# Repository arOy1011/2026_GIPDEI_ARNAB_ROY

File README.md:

<p align="center">📟 NAPPNU Motion Data Recorder</p>

<p align="center">
Bluetooth-enabled Motion Data Logger built using the <b>Seeed XIAO nRF52840 Sense</b>.
</p>
---

# 🛠 Hardware Components

| Component | Quantity |
|-----------|:--------:|
| Seeed XIAO nRF52840 Sense | 1 |
| DS3231 RTC Module | 1 |
| microSD Card Module | 1 |
| microSD Card (FAT32) | 1 |
| Push Button | 1 |
| Li-Po Battery (3.7 V) | 1 |
| USB Type-C Cable | 1 |

---
<div style="page-break-after: always;"></div>

# 📂 Project Structure

```text
main-folder/
│
├── Mobile Application/
│.  └── motion-logger
│      		└── files.....
│
├── Code-Hardware/
│   └── Data_Logger.ino
│
├── PCB Design/
│   └── KiCAD.zip
│
├── Python-Script/
│   └── connect.py
│
└── README files
```

---

# 💻 Software Requirements

## Firmware Development

- Arduino IDE 2.x
- Seeed nRF52 Board Package

### Required Arduino Libraries

- Adafruit Bluefruit nRF52 Libraries
- LSM6DS3
- SdFat
- RTClib
- Wire
- SPI
- EEPROM

---
<div style="page-break-after: always;"></div>

## 📦 Project Files

All required project files are available in the shared Google Drive folder below.

> 📁 **Download Project Files**  
> https://drive.google.com/drive/folders/1yOiiscPsLclZifj_FWon-T-I5wJ6or7X?usp=drive_link

The folder contains:

- 📱 Pre-built Android APK
- 📱 Flutter source code

---

## 📱 Option 1 — Install the Pre-built APK (Recommended)

1. Open the **Google Drive** folder above.
2. Navigate to:

```
Android-Application/
└── motion_logger/
    └── build/
        └── app/
            └── outputs/
                └── flutter-apk/
                    └── app-release.apk
```

3. Download **app-release.apk** to your Android device.([click here](https://drive.google.com/file/d/1uAppkaTGrx7KVFIq7DyhZL77ZsfjcmHu/view?usp=drive_link))
4. Install the APK.

> **Note:** Enable **Install from Unknown Sources** if prompted.

---

## 👨‍💻 Option 2 — Development Setup

Download the complete project from the Google Drive folder.

### Flutter

```bash
cd motion_logger

flutter pub get

flutter run
```

Generate a release APK:

```bash
flutter build apk --release
```

The generated APK will be available at:

```

build/app/outputs/flutter-apk/app-release.apk

```

---

## Flutter Packages Used

- flutter_blue_plus
- permission_handler
- file_picker
- shared_preferences
- url_launcher
- path_provider

---
## Desktop Client

- Python 3.11+
- Bleak

```bash
pip install bleak
```

---
<div style="page-break-after: always;"></div>

# 🚀 Setup Procedure

## 📱 Device Controls

| Button Action | Function |
|--------------|----------|
| 🟢 Single Press | Start / Stop Logging |
| 🔵 Double Press | Enable / Disable BLE |
| 🔴 Long Press (1.5 s) | Enter Deep Sleep |
| 🟡 Single Press (Wake) | Wake Device |

---

## Step 1 — Upload Firmware

Open

```txt
1.Install and run Arduino ide with the Required arduino libraries(mentioned above)
2.Download Code-Hardware/Data_Logger.ino from drive
```

Select

```
Board
    ↓
Seeed XIAO nRF52840 Sense
```

Then click **Upload**.

---

## Step 2 — Prepare the SD Card

- Format as **FAT32**
- Insert into the SD card module

---
<div style="page-break-after: always;"></div>

## 📱 Step 3 — Client Applications

After building the firmware and mobile application, the Motion Data Logger can be controlled using **either** the Android application **or** the Desktop Python client.

> **Important**
>
> Only **one client can be connected to the logger at a time.**
>
> - ✅ Android Application **or**
> - ✅ Desktop Python Client
> - ❌ Both simultaneously

> **Note**
>
> Press the device button **twice** to enable **BLE advertising mode**. The logger advertises for **30 seconds**, allowing the Android application to discover and connect to it. If a connection is established within this interval, the device remains connected and is ready for normal operation until disconnected.
---
<div style="page-break-after: always;"></div>

### 3.1.Android Application

The Android application provides a graphical interface for controlling the logger and managing stored CSV files.

---

#### 1. Device Discovery

- Scan for nearby MotionLogger devices.
- Select a device from the list.
- Connect using Bluetooth Low Energy (BLE).

<p align="center">

&nbsp;&nbsp;

</p>

---
<div style="page-break-after: always;"></div>

#### 2. Logger Control

After connecting, the application allows you to:

- Start logging
- Stop logging
- View logger status

---

#### 3. File Management

The application can communicate directly with the logger to:

- View all CSV files
- Download selected files
- Delete files from the SD card
- Refresh the file list

---

### 3.2.Desktop Client

A lightweight Python client is also provided for communicating with the logger from a computer.

The desktop client supports:

- Device discovery
- BLE connection
- Start / Stop logging
- View logger status
- List stored files
- Download files
- Delete files

Run the client->
```bash
cd path
python connect.py
```

---

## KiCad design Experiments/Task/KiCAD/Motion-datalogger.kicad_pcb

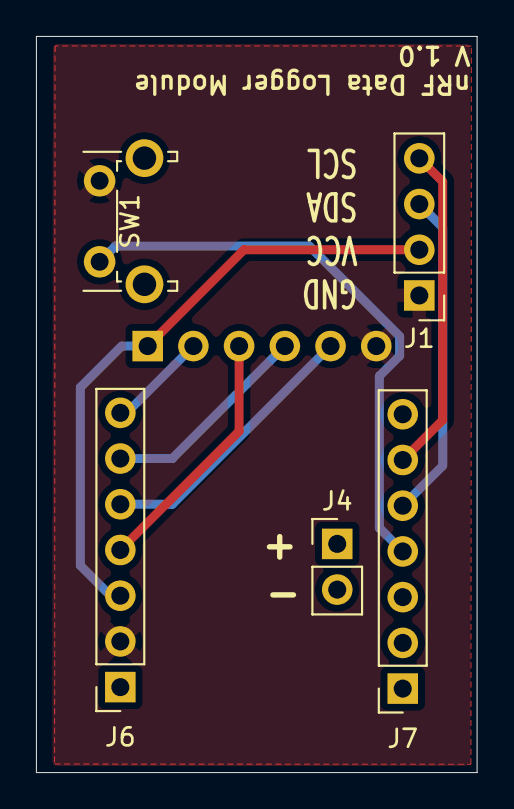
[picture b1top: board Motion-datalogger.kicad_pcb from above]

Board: 2 copper layers, 24.5 x 40.9 mm, 6 parts (1 on the bottom side), 9 nets.

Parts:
J1: Conn_01x04; PinHeader_1x04_P2.54mm_Vertical
J2: Conn_01x06; PinHeader_1x06_P2.54mm_Vertical
J4: Conn_01x02_Pin; PinHeader_1x02_P2.54mm_Vertical
J6, J7: Conn_01x07_Socket; PinSocket_1x07_P2.54mm_Vertical
SW1: SW_Push; SW_Tactile_SPST_Angled_PTS645Vx58-2LFS

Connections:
GND: J1.1, J2.6, J6.2, SW1.2
unnamed: J1.3, J7.5
unnamed: J1.4, J7.6
unnamed: J2.2, J6.7
unnamed: J2.3, J6.4
unnamed: J2.4, J6.6
unnamed: J2.5, J6.5
unnamed: J7.4, SW1.1
PWR_FLAG: J1.2, J2.1, J6.3

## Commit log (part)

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2026-05-18 vault backup: 2026-05-18 14:17:01
2026-05-18 vault backup: 2026-05-18 14:17:47
2026-05-18 vault backup: 2026-05-18 14:23:14
2026-05-18 vault backup: 2026-05-18 15:21:04
2026-05-18 vault backup: 2026-05-18 16:29:35
2026-05-18 vault backup: 2026-05-18 20:12:34
2026-05-19 vault backup: 2026-05-19 13:19:03
2026-05-19 vault backup: 2026-05-19 14:06:09
2026-05-19 vault backup: 2026-05-19 15:12:29
2026-05-19 vault backup: 2026-05-19 15:54:26
2026-05-19 vault backup: 2026-05-19 16:02:24
2026-05-19 vault backup: 2026-05-20 02:20:47
2026-05-20 vault backup: 2026-05-20 15:23:54
2026-05-20 vault backup: 2026-05-20 16:57:27
2026-05-21 vault backup: 2026-05-21 14:33:09
2026-05-21 vault backup: 2026-05-21 14:36:02
2026-05-21 vault backup: 2026-05-21 14:42:36
2026-05-21 vault backup: 2026-05-21 16:55:43
2026-05-22 vault backup: 2026-05-22 09:54:43
2026-05-22 vault backup: 2026-05-22 15:21:45
2026-05-22 vault backup: 2026-05-22 17:17:09
2026-05-22 vault backup: 2026-05-22 17:19:31
2026-05-22 vault backup: 2026-05-22 17:36:47
2026-05-25 vault backup: 2026-05-25 11:03:39
2026-05-25 vault backup: 2026-05-25 11:03:55
2026-05-26 vault backup: 2026-05-26 10:33:28
2026-05-26 vault backup: 2026-05-26 15:57:51
2026-05-26 vault backup: 2026-05-26 23:29:26
2026-06-01 vault backup: 2026-06-01 15:42:48
2026-06-01 vault backup: 2026-06-01 15:52:12
2026-06-02 vault backup: 2026-06-02 09:44:27
2026-06-02 vault backup: 2026-06-02 10:50:56
2026-06-02 vault backup: 2026-06-02 16:24:12
2026-06-02 vault backup: 2026-06-02 16:57:23
2026-06-05 vault backup: 2026-06-05 09:55:42
2026-06-08 vault backup: 2026-06-08 10:42:08
2026-06-08 vault backup: 2026-06-08 15:47:02
2026-06-08 vault backup: 2026-06-08 17:19:44
2026-06-11 vault backup: 2026-06-11 16:30:32
2026-06-11 vault backup: 2026-06-11 16:33:52
2026-06-11 vault backup: 2026-06-11 16:36:39
2026-06-14 vault backup: 2026-06-14 18:20:09
2026-06-25 vault backup: 2026-06-25 19:43:02
2026-06-25 vault backup: 2026-06-25 19:45:07
